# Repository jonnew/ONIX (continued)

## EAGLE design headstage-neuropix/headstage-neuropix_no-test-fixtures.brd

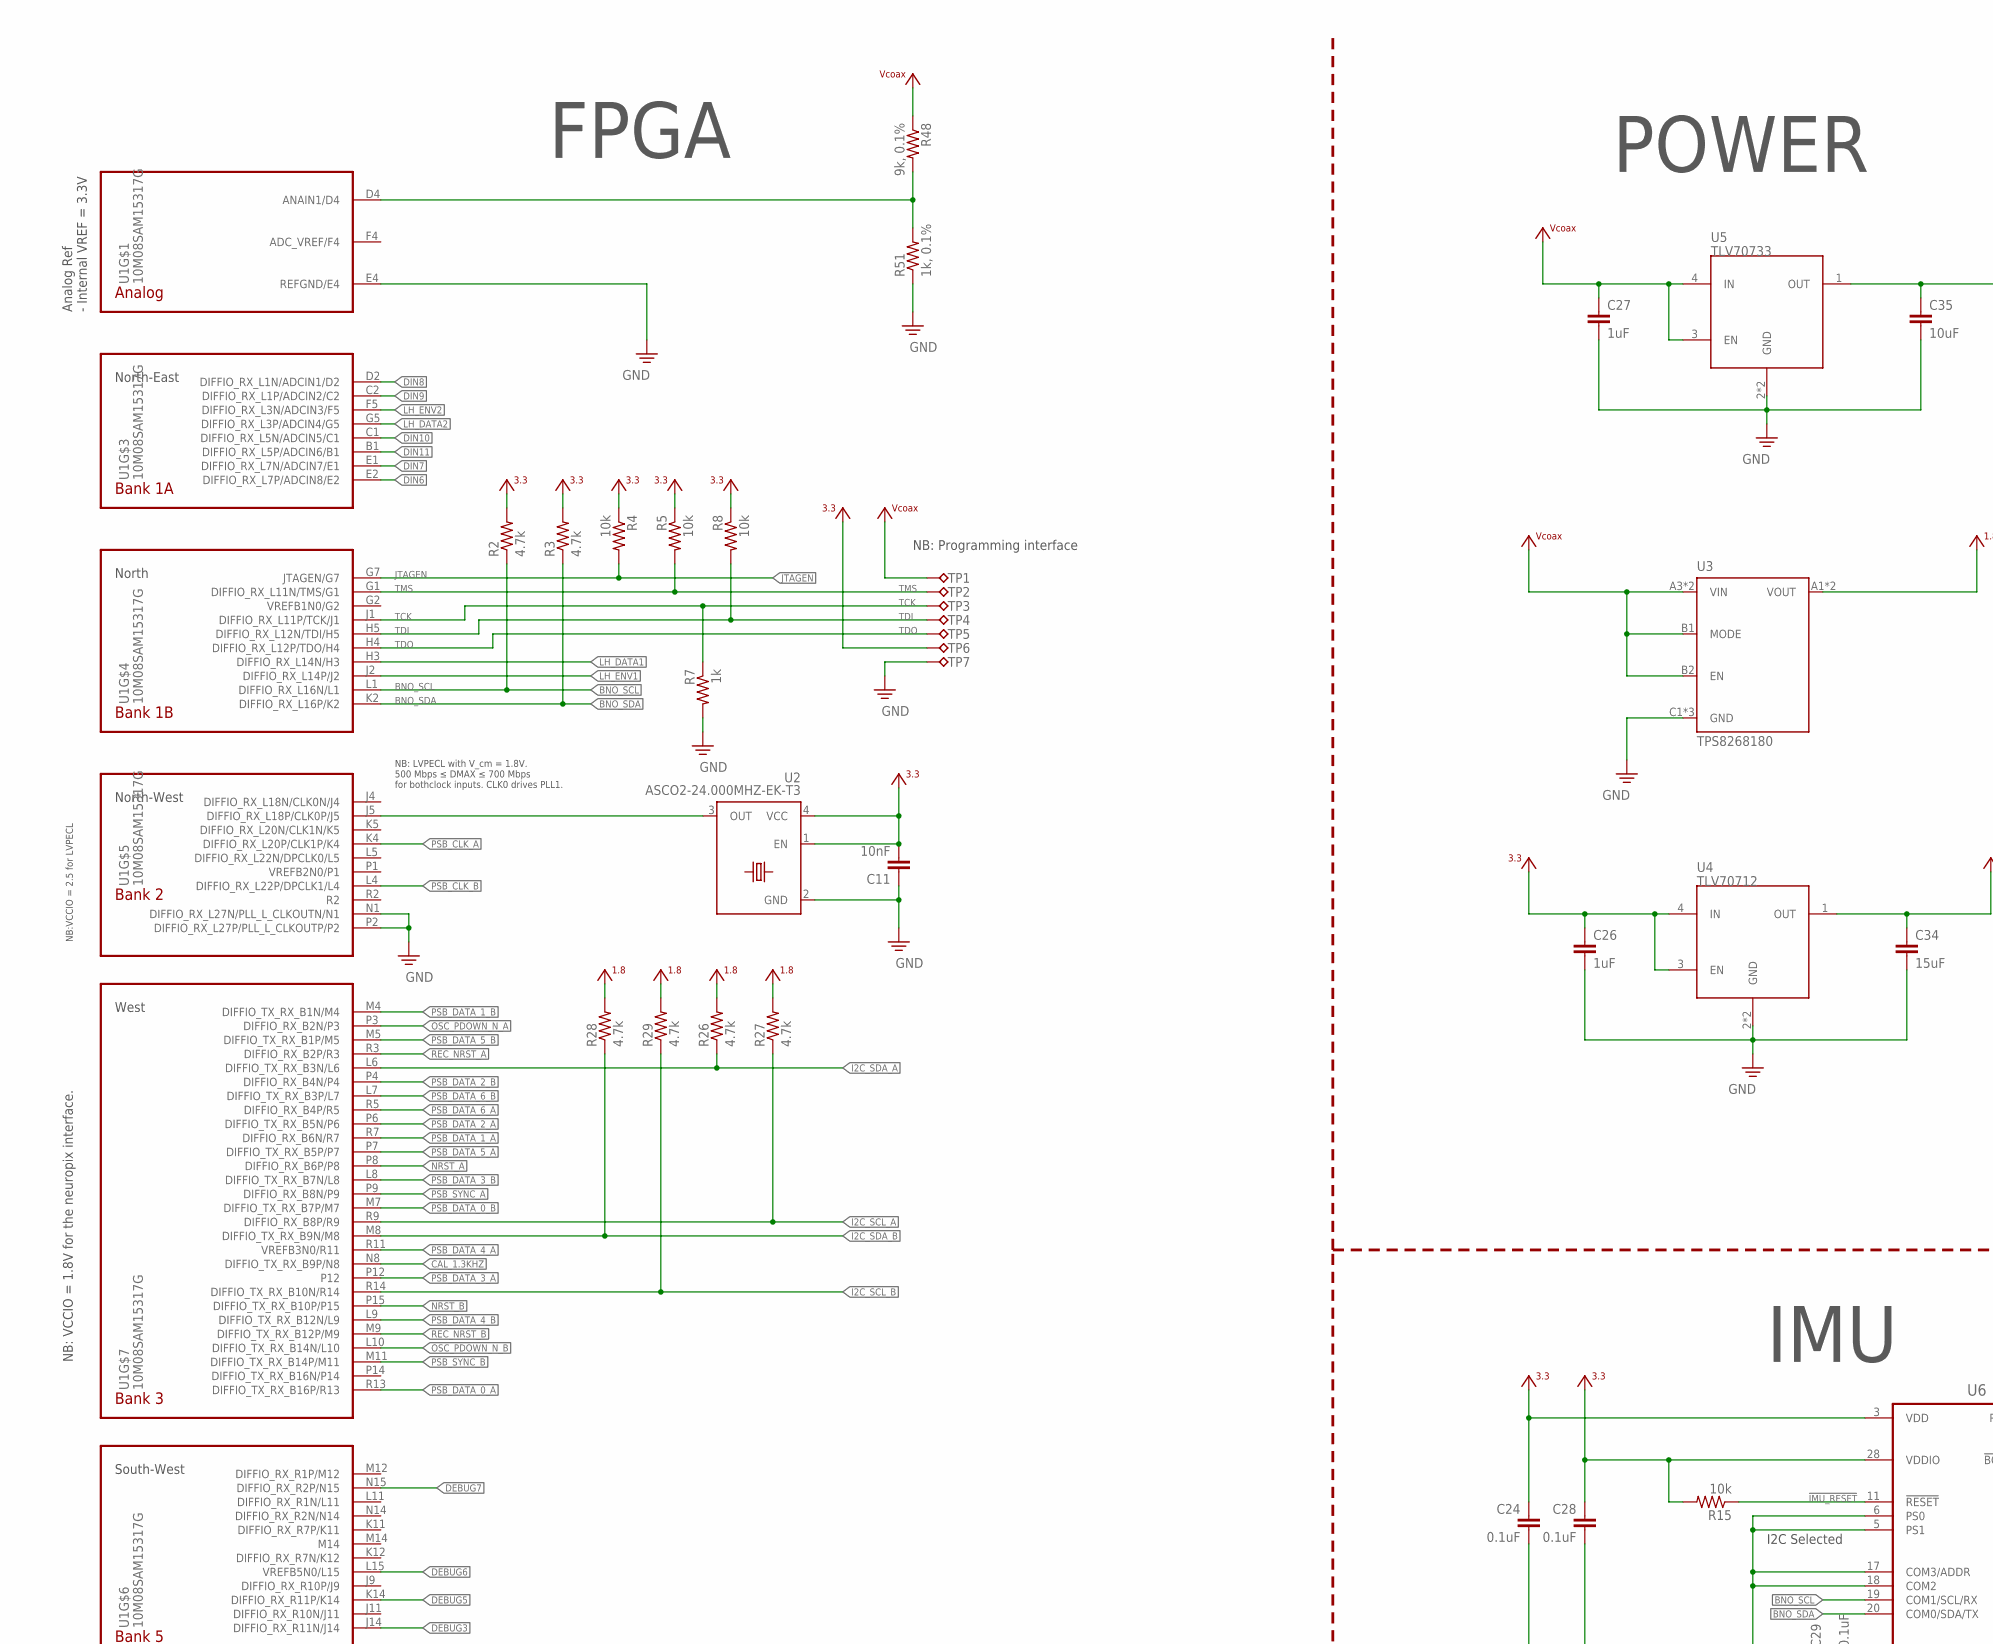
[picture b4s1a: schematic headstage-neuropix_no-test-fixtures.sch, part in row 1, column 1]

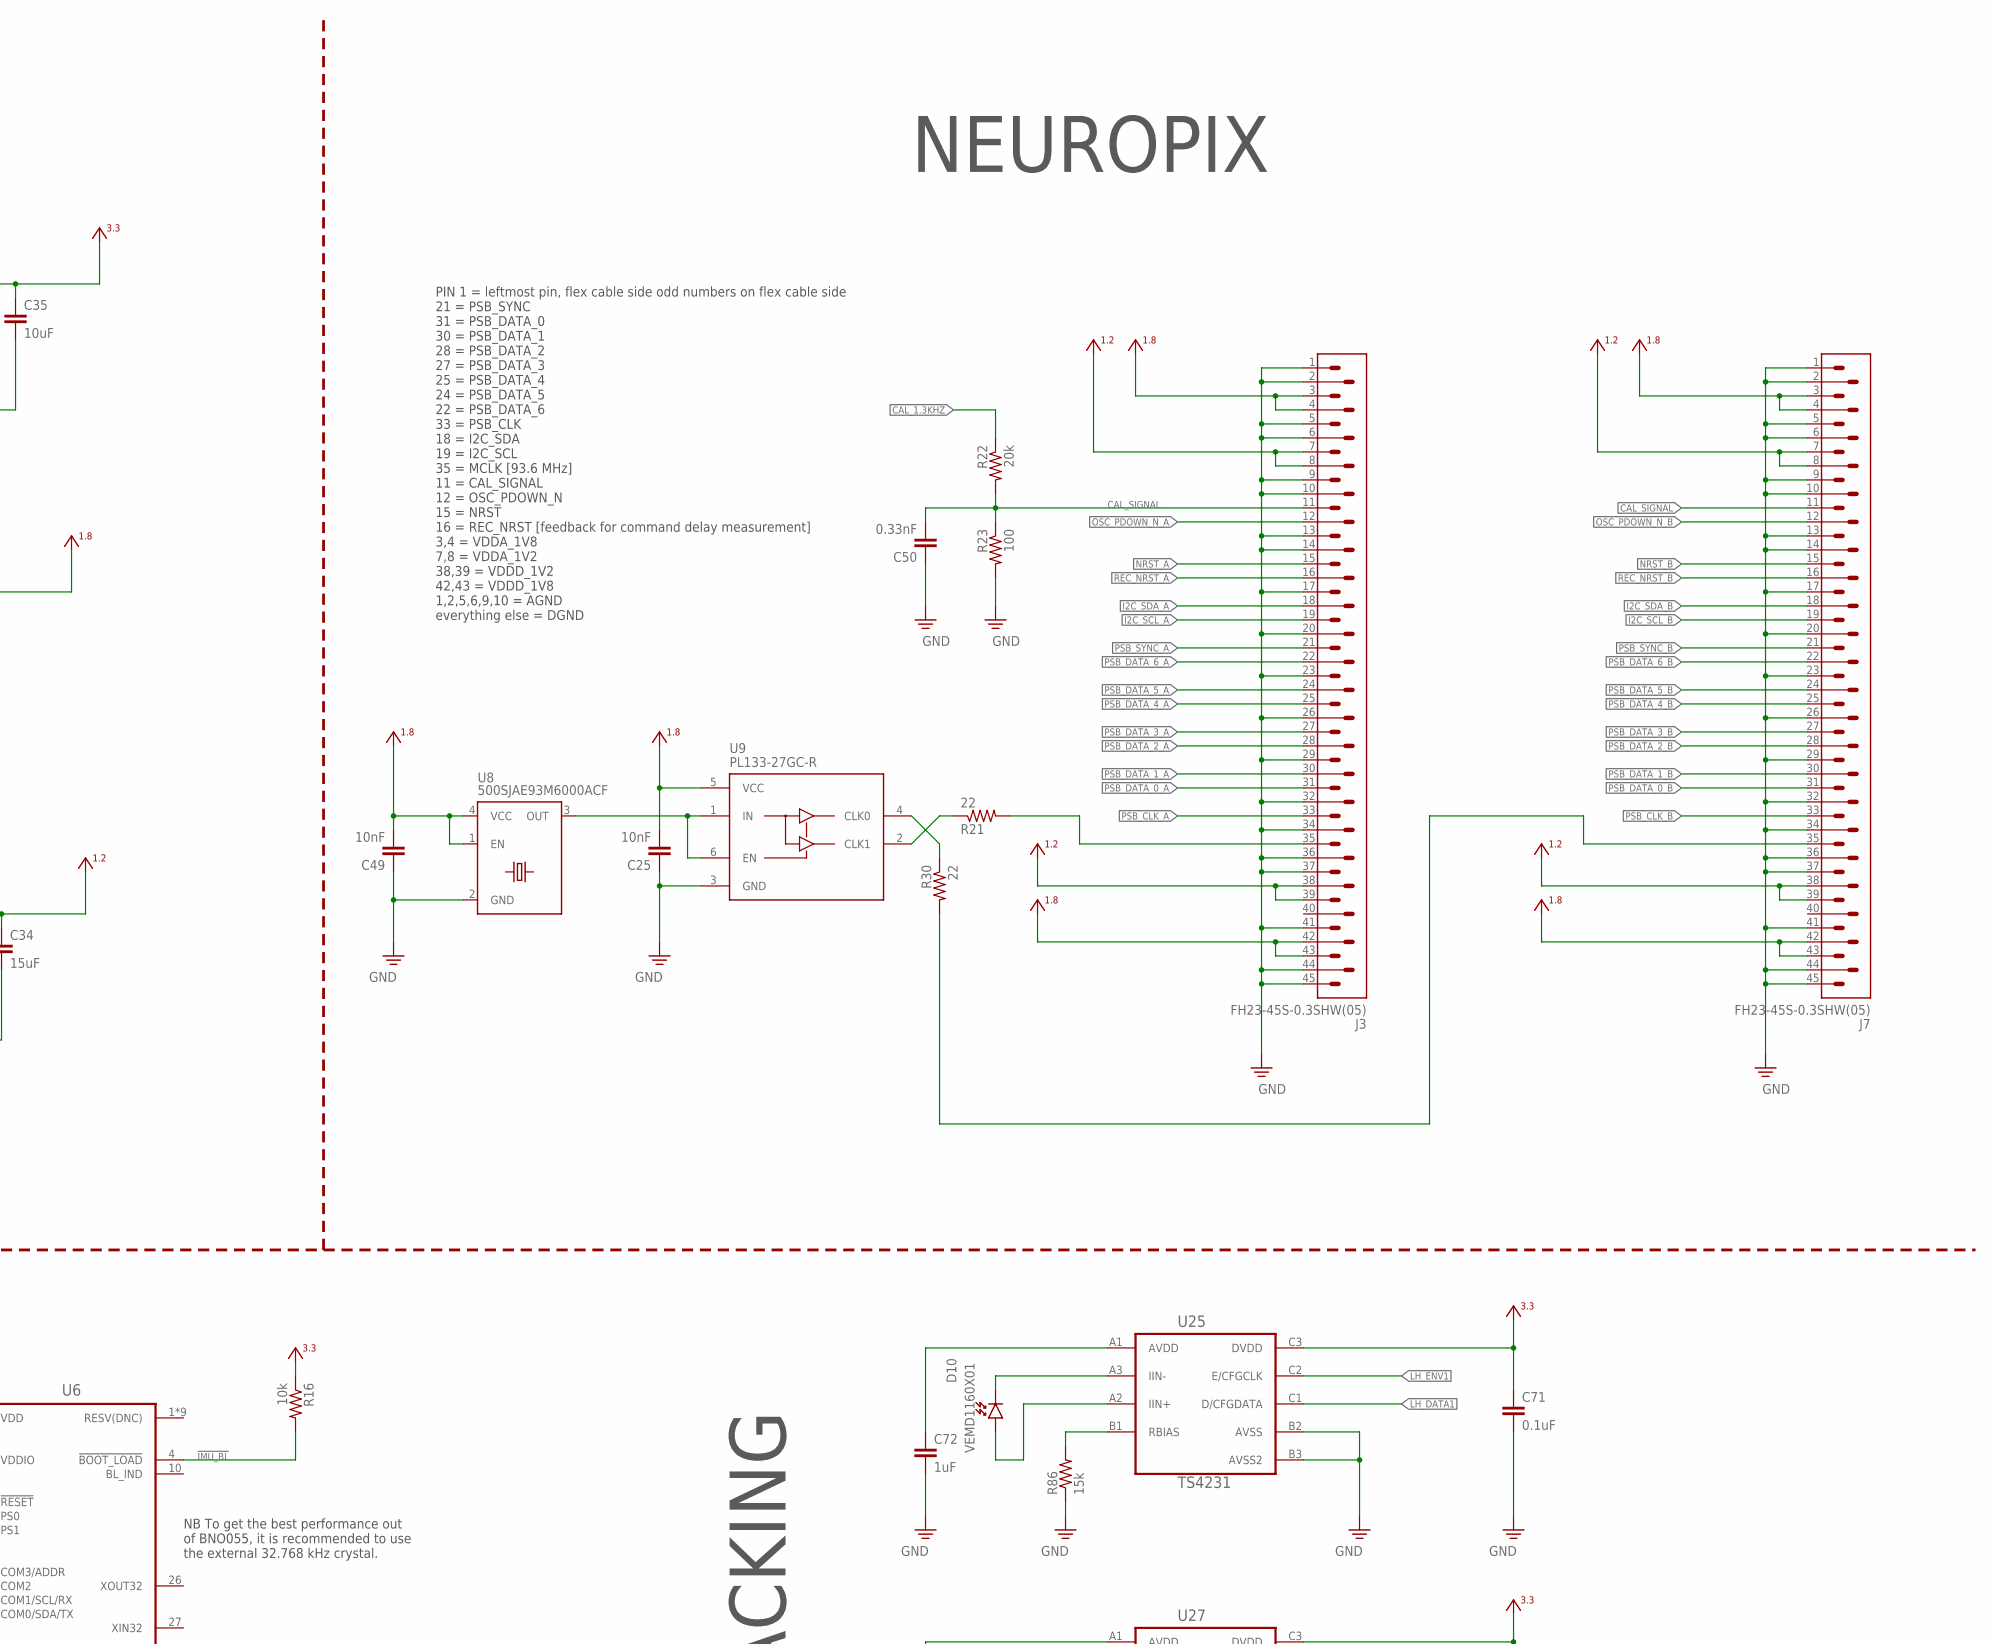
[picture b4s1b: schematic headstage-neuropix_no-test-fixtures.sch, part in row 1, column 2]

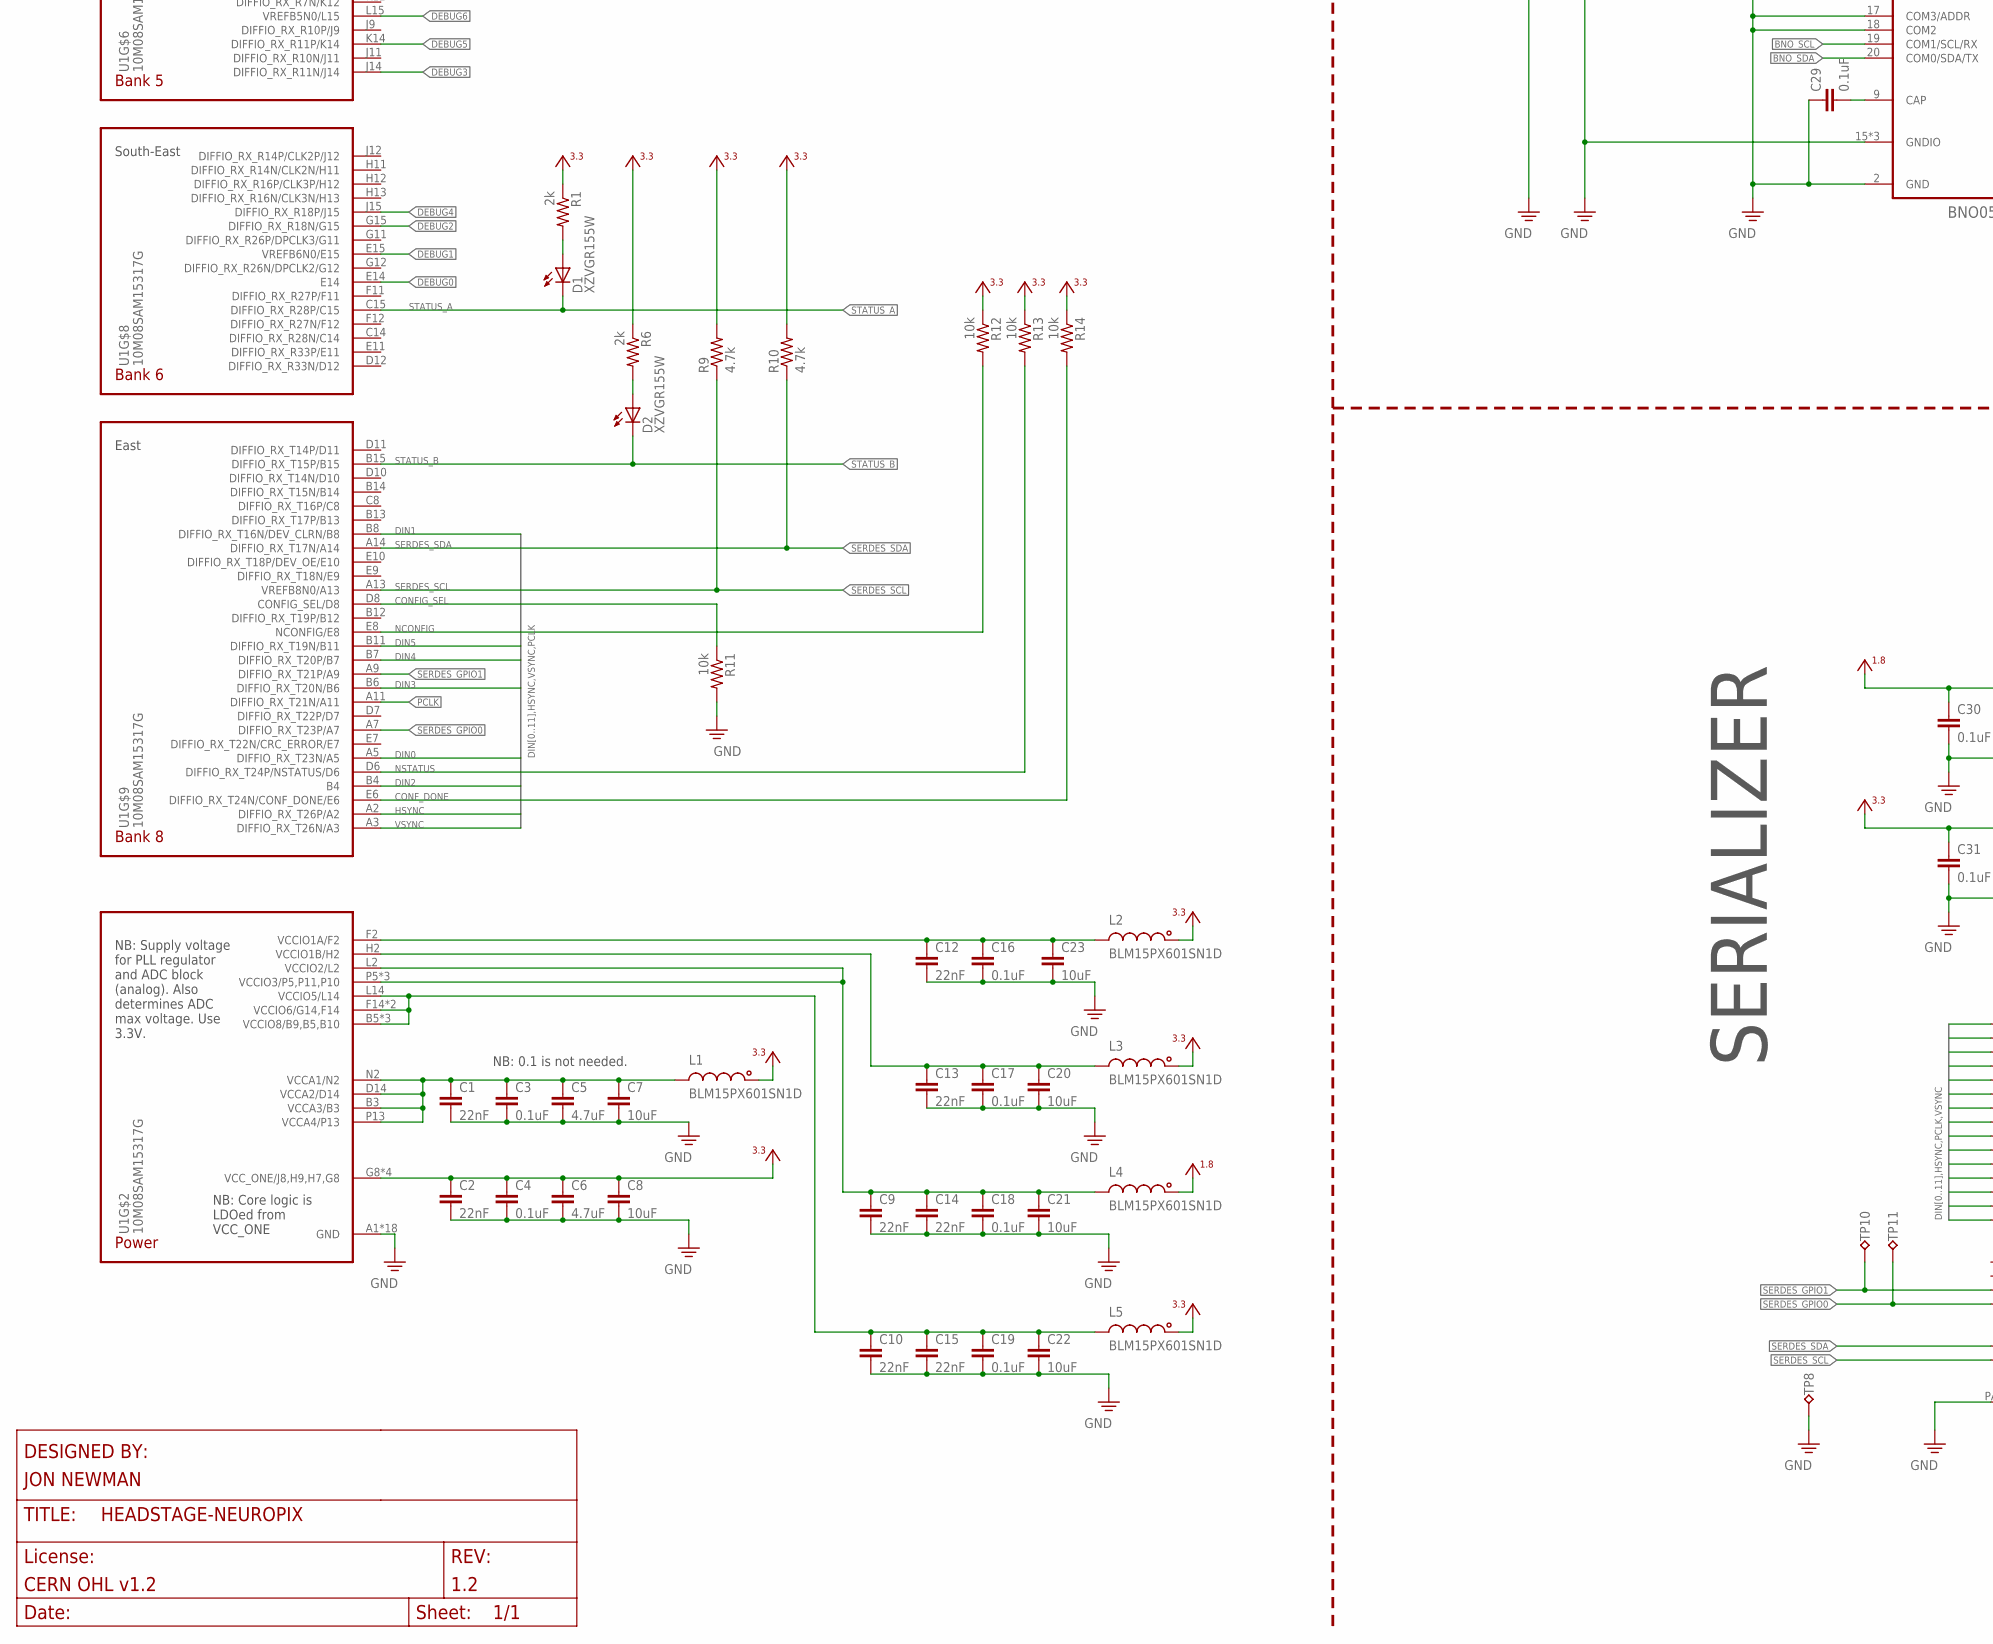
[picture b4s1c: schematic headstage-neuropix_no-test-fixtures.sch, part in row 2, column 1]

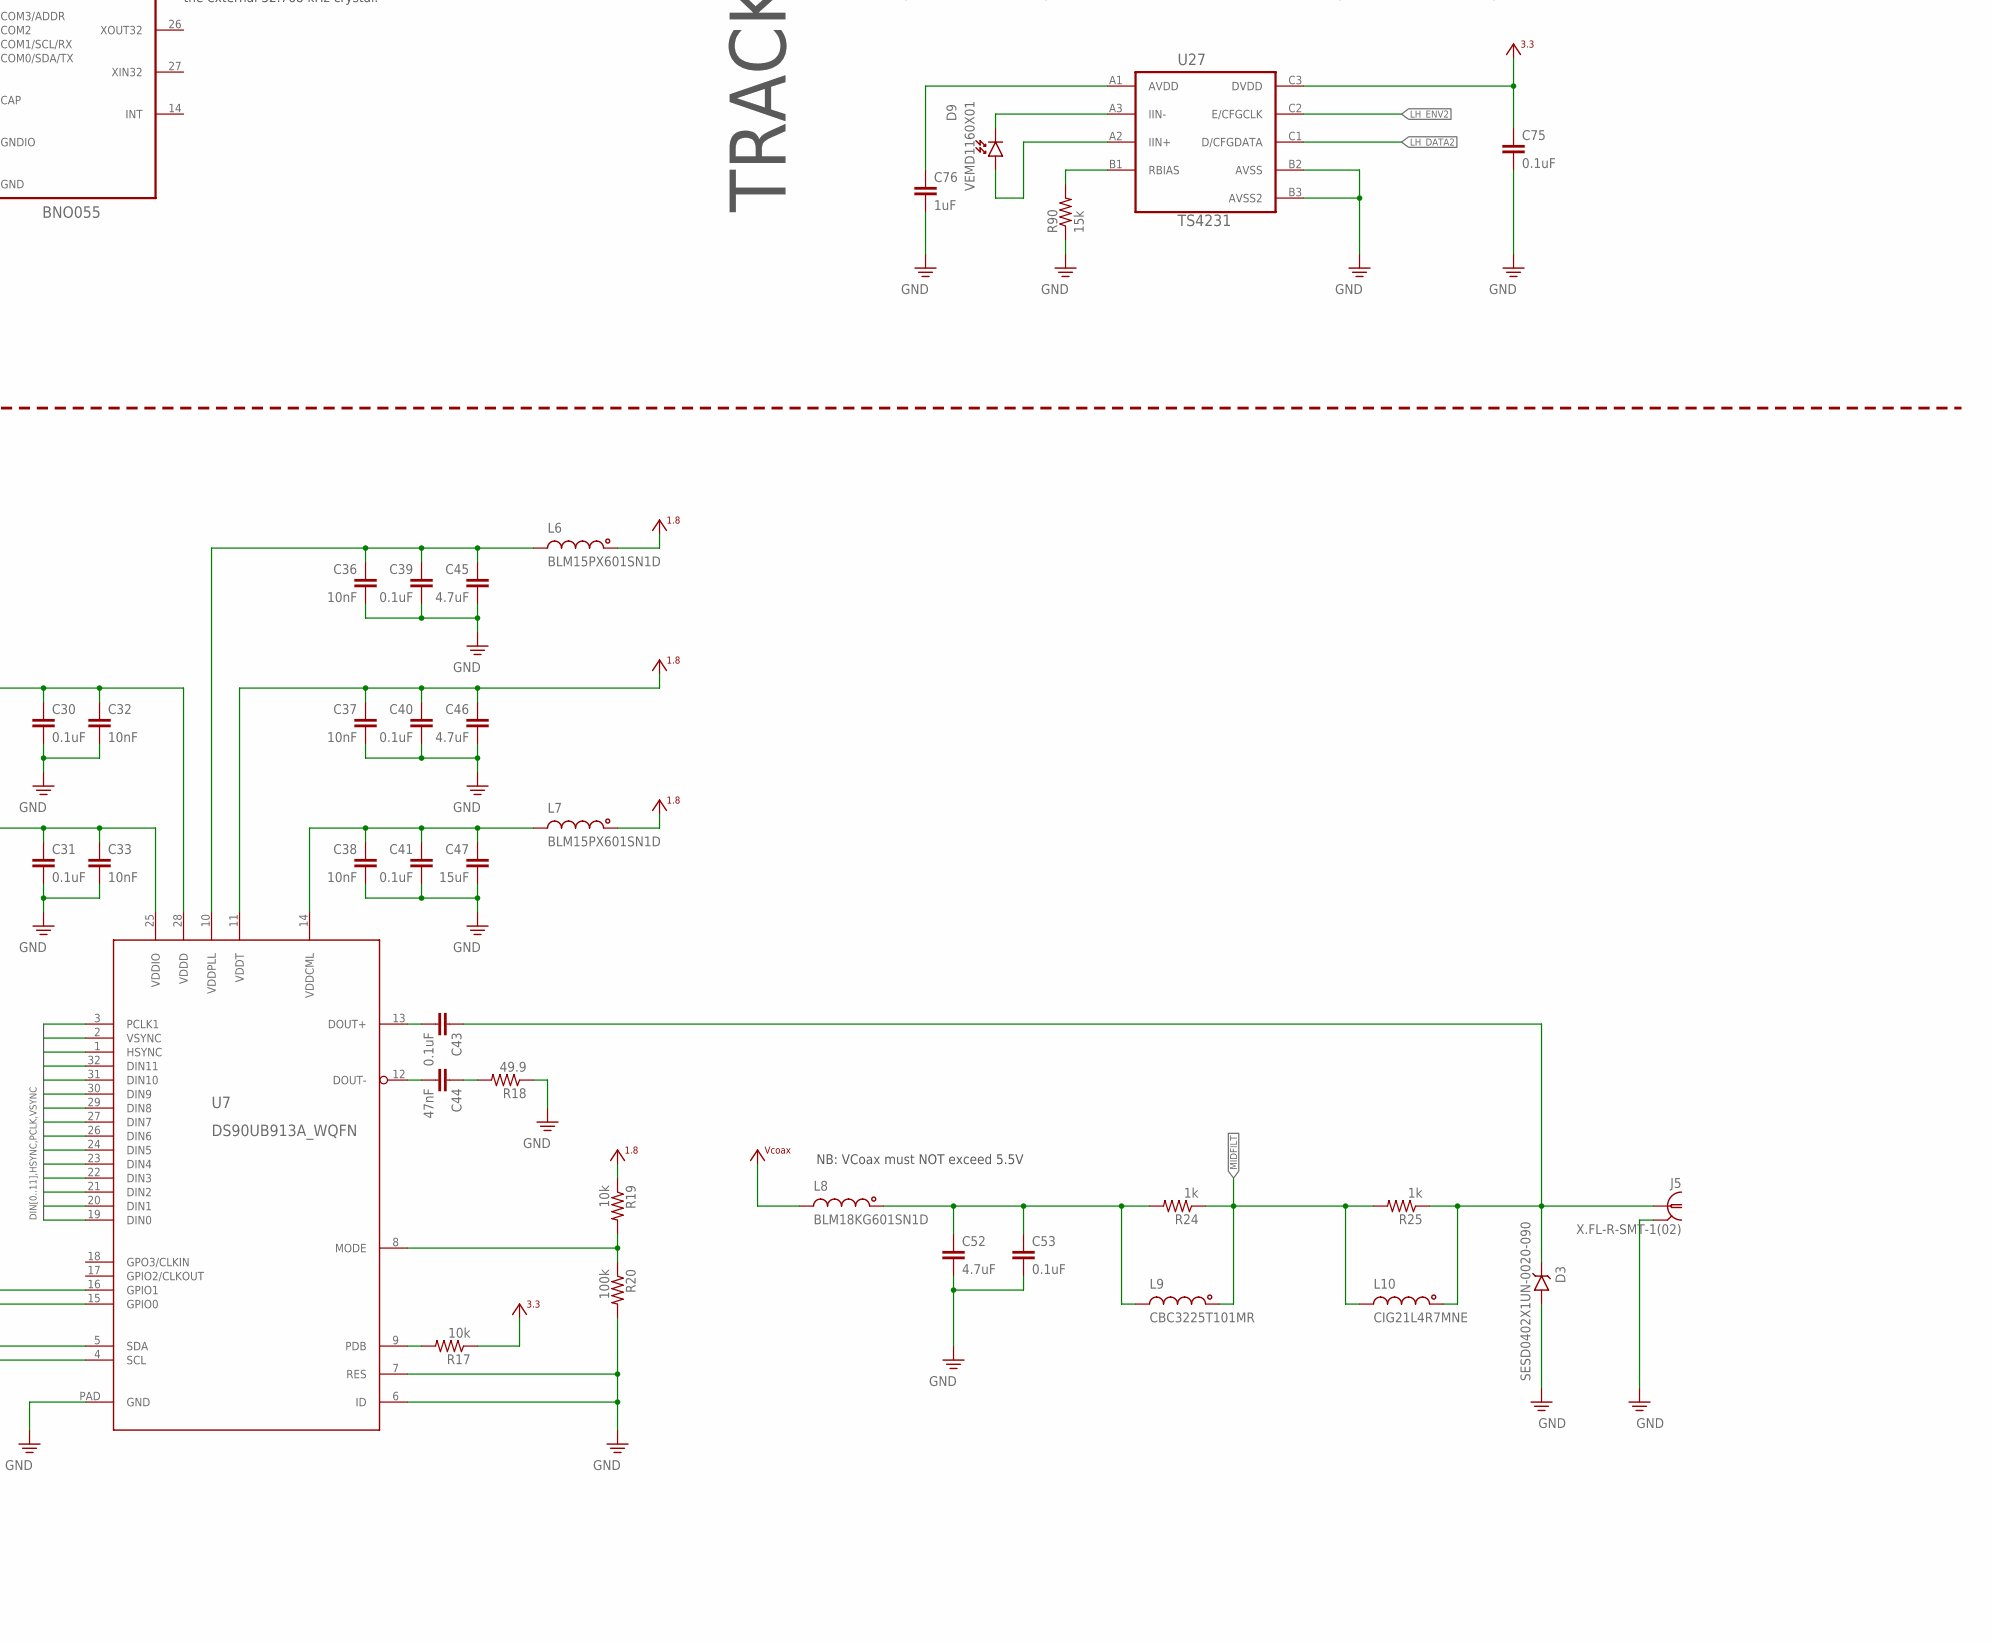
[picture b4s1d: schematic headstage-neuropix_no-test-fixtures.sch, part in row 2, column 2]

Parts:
C1, C2, C9, C10, C12, C13, C14, C15: 22nF; 0201T
C3, C4, C16, C17, C18, C19, C24, C28, C29, C30, C31, C39, C40, C41, C43, C53: 0.1uF; 0201T
C5, C6, C45, C46, C52: 4.7uF; 0402T
C7, C8, C20, C21, C22, C23, C35: 10uF; 0402T
C11, C25, C32, C33, C36, C37, C38, C49: 10nF; 0201T
C26, C27: 1uF; 0402T
C34, C47: 15uF; 0402TW
C44: 47nF; 0201T
C50: 0.33nF; 0201T
C71, C75: 0.1uF; 0201T; PARTNO C0603X5R1C104K030BC
C72, C76: 1uF; 0201T; PARTNO CL03A105MP3ZSNH
D1, D2: XZVGR155W; LED-0201T
D3: SESD0402X1UN-0020-090; 0402T-DFN
D9, D10: VEMD1160X01; 0805PT
J3, J7: FH23-45S-0.3SHW(05)
J5: X.FL-R-SMT-1(02); X_FL_R_SMT_1(02)
L1, L2, L3, L4, L5, L6, L7: BLM15PX601SN1D; 0402T
L8: BLM18KG601SN1D; 0603T
L9: CBC3225T101MR; 1210T
L10: CIG21L4R7MNE; 0805T
R1, R6: 2k; 0201T
R2, R3, R9, R10, R26, R27, R28, R29: 4.7k; 0201T
R4, R5, R8, R11, R12, R13, R14, R15, R16, R17, R19: 10k; 0201T
R7, R24, R25: 1k; 0201T
R18: 49.9; 0201T
R20: 100k; 0201T
R21, R30: 22; 0201T
R22: 20k; 0201T
R23: 100; 0201T
R48: 9k, 0.1%; 0201T
R51: 1k, 0.1%; 0201T
R86, R90: 15k; 0201T
TP1, TP2, TP3, TP4, TP5, TP6, TP7: TPTP10R; TP10R
TP8: TPTP11R; TP11R
TP10, TP11: TPTP09R; TP09R
U1: 10M08SAM15317G; MBGA153-8X8
U2: ASCO2-24.000MHZ-EK-T3; ASCO
U3: TPS8268180; MICROSIP9-3X2.3
U4: TLV70712; X2SON
U5: TLV70733; X2SON
U6: BNO055; LGA-28-3.8X5.2
U7: DS90UB913A_WQFN; WQFN32-5X5
U8: 500SJAE93M6000ACF; SIT8008BCA7-18E
U9: PL133-27GC-R; DFN6_2X1.3_PAD
U25, U27: TS4231; WLCSP3X3

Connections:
24MHZ_P: U1.J5 (DIFFIO_RX_L18P/CLK0P/J5), U2.3 (OUT)
!IMU_BL: R16.2, U6.4 (!BOOT_LOAD)
!IMU_RESET: R15.1, U6.11 (!RESET)
+1V2: C34.1, J3.7, J3.8, J3.38, J3.39, J7.7, J7.8, J7.38, J7.39, U4.1 (OUT)
+1V8: C25.2, C30.1, C32.1, C37.1, C40.1, C46.1, C49.2, J3.3, J3.4, J3.42, J3.43, J7.3, J7.4, J7.42, J7.43, L4.1, L6.1, L7.1, R19.1, R26.2, R27.2, R28.2, R29.2, U3.A1 (VOUT), U3.A2 (VOUT), U7.11 (VDDT), U7.28 (VDDD), U8.1 (EN), U8.4 (VCC), U9.5 (VCC)
+3V3: C2.1, C4.1, C6.1, C8.1, C11.2, C24.1, C26.1, C28.1, C31.1, C33.1, C35.1, C71.1, C75.1, L1.1, L2.1, L3.1, L5.1, R1.1, R2.2, R3.2, R4.1, R5.1, R6.1, R8.1, R9.2, R10.2, R12.1, R13.1, R14.1, R15.2, R16.1, R17.1, TP6.TP, U1.G8 (VCC_ONE/J8,H9,H7,G8), U1.H7 (VCC_ONE/J8,H9,H7,G8), U1.H9 (VCC_ONE/J8,H9,H7,G8), U1.J8 (VCC_ONE/J8,H9,H7,G8), U2.1 (EN), U2.4 (VCC), U4.3 (EN), U4.4 (IN), U5.1 (OUT), U6.3 (VDD), U6.28 (VDDIO), U7.25 (VDDIO), U25.C3 (DVDD), U27.C3 (DVDD)
BNO_SCL: R2.1, U1.L1 (DIFFIO_RX_L16N/L1), U6.19 (COM1/SCL/RX)
BNO_SDA: R3.1, U1.K2 (DIFFIO_RX_L16P/K2), U6.20 (COM0/SDA/TX)
CAL_1.3KHZ: R22.1, U1.N8 (DIFFIO_TX_RX_B9P/N8)
CAL_SIGNAL: C50.2, J3.11, J7.11, R22.2, R23.1
CONFIG_SEL: R11.1, U1.D8 (CONFIG_SEL/D8)
CONF_DONE: R14.2, U1.E6 (DIFFIO_RX_T24N/CONF_DONE/E6)
DEBUG0: U1.E14
DEBUG1: U1.E15 (VREFB6N0/E15)
DEBUG2: U1.G15 (DIFFIO_RX_R18N/G15)
DEBUG3: U1.J14 (DIFFIO_RX_R11N/J14)
DEBUG4: U1.J15 (DIFFIO_RX_R18P/J15)
DEBUG5: U1.K14 (DIFFIO_RX_R11P/K14)
DEBUG6: U1.L15 (VREFB5N0/L15)
DEBUG7: U1.N15 (DIFFIO_RX_R2P/N15)
DIN0: U1.A5 (DIFFIO_RX_T23N/A5), U7.19 (DIN0)
DIN1: U1.B8 (DIFFIO_RX_T16N/DEV_CLRN/B8), U7.20 (DIN1)
DIN2: U1.B4, U7.21 (DIN2)
DIN3: U1.B6 (DIFFIO_RX_T20N/B6), U7.22 (DIN3)
DIN4: U1.B7 (DIFFIO_RX_T20P/B7), U7.23 (DIN4)
DIN5: U1.B11 (DIFFIO_RX_T19N/B11), U7.24 (DIN5)
DIN6: U1.E2 (DIFFIO_RX_L7P/ADCIN8/E2), U7.26 (DIN6)
DIN7: U1.E1 (DIFFIO_RX_L7N/ADCIN7/E1), U7.27 (DIN7)
DIN8: U1.D2 (DIFFIO_RX_L1N/ADCIN1/D2), U7.29 (DIN8)
DIN9: U1.C2 (DIFFIO_RX_L1P/ADCIN2/C2), U7.30 (DIN9)
DIN10: U1.C1 (DIFFIO_RX_L5N/ADCIN5/C1), U7.31 (DIN10)
DIN11: U1.B1 (DIFFIO_RX_L5P/ADCIN6/B1), U7.32 (DIN11)
GND: C1.2, C2.2, C3.2, C4.2, C5.2, C6.2, C7.2, C8.2, C9.2, C10.2, C11.1, C12.2, C13.2, C14.2, C15.2, C16.2, C17.2, C18.2, C19.2, C20.2, C21.2, C22.2, C23.2, C24.2, C25.1, C26.2, C27.2, C28.2, C29.1, C30.2, C31.2, C32.2, C33.2, C34.2, C35.2, C36.2, C37.2, C38.2, C39.2, C40.2, C41.2, C45.2, C46.2, C47.2, C49.1, C50.1, C52.2, C53.2, C71.2, C72.2, C75.2, C76.2, D3.A, J3.1, J3.2, J3.5, J3.6, J3.9, J3.10, J3.13, J3.14, J3.17, J3.20, J3.23, J3.26, J3.29, J3.32, J3.34, J3.36, J3.37, J3.41, J3.44, J3.45, J5.P$2 (2), J5.P$3 (2), J5.P$4 (2), J7.1, J7.2, J7.5, J7.6, J7.9, J7.10, J7.13, J7.14, J7.17, J7.20, J7.23, J7.26, J7.29, J7.32, J7.34, J7.36, J7.37, J7.41, J7.44, J7.45, R7.2, R11.2, R18.1, R20.2, R23.2, R51.1, R86.1, R90.1, TP7.TP, TP8.TP, U1.A1 (GND), U1.A15 (GND), U1.B2 (GND), U1.D5 (GND), U1.D9 (GND), U1.E4 (REFGND/E4), U1.E5 (GND), U1.E12 (GND), U1.G4 (GND), U1.G9 (GND), U1.H8 (GND), U1.H14 (GND), U1.J7 (GND), U1.L12 (GND), U1.M2 (GND), U1.M6 (GND), U1.M10 (GND), U1.N1 (DIFFIO_RX_L27N/PLL_L_CLKOUTN/N1), U1.P2 (DIFFIO_RX_L27P/PLL_L_CLKOUTP/P2), U1.R1 (GND), U1.R15 (GND), U2.2 (GND), U3.C1 (GND), U3.C2 (GND), U3.C3 (GND), U4.2 (GND), U4.PAD (GND), U5.2 (GND), U5.PAD (GND), U6.2 (GND), U6.5 (PS1), U6.6 (PS0), U6.15 (GNDIO), U6.16 (GNDIO), U6.17 (COM3/ADDR), U6.18 (COM2), U6.25 (GNDIO), U7.6 (ID), U7.7 (RES), U7.PAD (GND), U8.2 (GND), U9.3 (GND), U25.B2 (AVSS), U25.B3 (AVSS2), U27.B2 (AVSS), U27.B3 (AVSS2)
HSYNC: U1.A2 (DIFFIO_RX_T26P/A2), U7.1 (HSYNC)
I2C_SCL_A: J3.19, R27.1, U1.R9 (DIFFIO_RX_B8P/R9)
I2C_SCL_B: J7.19, R29.1, U1.R14 (DIFFIO_TX_RX_B10N/R14)
I2C_SDA_A: J3.18, R26.1, U1.L6 (DIFFIO_TX_RX_B3N/L6)
I2C_SDA_B: J7.18, R28.1, U1.M8 (DIFFIO_TX_RX_B9N/M8)
JTAGEN: R4.2, U1.G7 (JTAGEN/G7)
LH_DATA1: U1.H3 (DIFFIO_RX_L14N/H3), U25.C1 (D/CFGDATA)
LH_DATA2: U1.G5 (DIFFIO_RX_L3P/ADCIN4/G5), U27.C1 (D/CFGDATA)
LH_ENV1: U1.J2 (DIFFIO_RX_L14P/J2), U25.C2 (E/CFGCLK)
LH_ENV2: U1.F5 (DIFFIO_RX_L3N/ADCIN3/F5), U27.C2 (E/CFGCLK)
MIDFILT: L9.1, L10.2, R24.1, R25.2
unnamed: U8.3 (OUT), U9.1 (IN), U9.6 (EN)
unnamed: R30.1, U9.4 (CLK0)
unnamed: J3.35, R21.2
unnamed: C13.1, C17.1, C20.1, L3.2, U1.H2 (VCCIO1B/H2)
unnamed: J7.35, R30.2
unnamed: R21.1, U9.2 (CLK1)
unnamed: D10.C, U25.A3 (IIN-)
unnamed: D10.A, U25.A2 (IIN+)
unnamed: R86.2, U25.B1 (RBIAS)
unnamed: C72.1, U25.A1 (AVDD)
unnamed: C52.1, C53.1, L8.1, L9.2, R24.2
unnamed: D9.C, U27.A3 (IIN-)
unnamed: D9.A, U27.A2 (IIN+)
unnamed: R90.2, U27.B1 (RBIAS)
unnamed: C43.2, U7.13 (DOUT+)
unnamed: R17.2, U7.9 (PDB)
unnamed: C44.2, U7.12 (DOUT-)
unnamed: C44.1, R18.2
unnamed: R19.2, R20.1, U7.8 (MODE)
unnamed: C36.1, C39.1, C45.1, L6.2, U7.10 (VDDPLL)
unnamed: C38.1, C41.1, C47.1, L7.2, U7.14 (VDDCML)
unnamed: C76.1, U27.A1 (AVDD)
unnamed: R48.2, R51.2, U1.D4 (ANAIN1/D4)
unnamed: C29.2, U6.9 (CAP)
unnamed: D2.2 (A), R6.2
unnamed: D1.2 (A), R1.2
NCONFIG: R12.2, U1.E8 (NCONFIG/E8)
NRST_A: J3.15, U1.P8 (DIFFIO_RX_B6P/P8)
NRST_B: J7.15, U1.P15 (DIFFIO_TX_RX_B10P/P15)
NSTATUS: R13.2, U1.D6 (DIFFIO_RX_T24P/NSTATUS/D6)
OSC_PDOWN_N_A: J3.12, U1.P3 (DIFFIO_RX_B2N/P3)
OSC_PDOWN_N_B: J7.12, U1.L10 (DIFFIO_TX_RX_B14N/L10)
PCLK: U1.A11 (DIFFIO_RX_T21N/A11), U7.3 (PCLK1)
PSB_CLK_A: J3.33, U1.K4 (DIFFIO_RX_L20P/CLK1P/K4)
PSB_CLK_B: J7.33, U1.L4 (DIFFIO_RX_L22P/DPCLK1/L4)
PSB_DATA_0_A: J3.31, U1.R13 (DIFFIO_TX_RX_B16P/R13)
PSB_DATA_0_B: J7.31, U1.M7 (DIFFIO_TX_RX_B7P/M7)
PSB_DATA_1_A: J3.30, U1.R7 (DIFFIO_RX_B6N/R7)
PSB_DATA_1_B: J7.30, U1.M4 (DIFFIO_TX_RX_B1N/M4)
PSB_DATA_2_A: J3.28, U1.P6 (DIFFIO_TX_RX_B5N/P6)
PSB_DATA_2_B: J7.28, U1.P4 (DIFFIO_RX_B4N/P4)
PSB_DATA_3_A: J3.27, U1.P12
PSB_DATA_3_B: J7.27, U1.L8 (DIFFIO_TX_RX_B7N/L8)
PSB_DATA_4_A: J3.25, U1.R11 (VREFB3N0/R11)
PSB_DATA_4_B: J7.25, U1.L9 (DIFFIO_TX_RX_B12N/L9)
PSB_DATA_5_A: J3.24, U1.P7 (DIFFIO_TX_RX_B5P/P7)
PSB_DATA_5_B: J7.24, U1.M5 (DIFFIO_TX_RX_B1P/M5)
PSB_DATA_6_A: J3.22, U1.R5 (DIFFIO_RX_B4P/R5)
PSB_DATA_6_B: J7.22, U1.L7 (DIFFIO_TX_RX_B3P/L7)
PSB_SYNC_A: J3.21, U1.P9 (DIFFIO_RX_B8N/P9)
PSB_SYNC_B: J7.21, U1.M11 (DIFFIO_TX_RX_B14P/M11)
REC_NRST_A: J3.16, U1.R3 (DIFFIO_RX_B2P/R3)
REC_NRST_B: J7.16, U1.M9 (DIFFIO_TX_RX_B12P/M9)
SERDES_GPIO0: TP11.TP, U1.A7 (DIFFIO_RX_T23P/A7), U7.15 (GPIO0)
SERDES_GPIO1: TP10.TP, U1.A9 (DIFFIO_RX_T21P/A9), U7.16 (GPIO1)
SERDES_SCL: R9.1, U1.A13 (VREFB8N0/A13), U7.4 (SCL)
SERDES_SDA: R10.1, U1.A14 (DIFFIO_RX_T17N/A14), U7.5 (SDA)
SIGOUT: C43.1, D3.C, J5.P$1 (1), L10.1, R25.1
STATUS_A: D1.1 (C), U1.C15 (DIFFIO_RX_R28P/C15)
STATUS_B: D2.1 (C), U1.B15 (DIFFIO_RX_T15P/B15)
TCK: R7.1, TP3.TP, U1.J1 (DIFFIO_RX_L11P/TCK/J1)
TDI: R8.2, TP4.TP, U1.H5 (DIFFIO_RX_L12N/TDI/H5)
TDO: TP5.TP, U1.H4 (DIFFIO_RX_L12P/TDO/H4)
TMS: R5.2, TP2.TP, U1.G1 (DIFFIO_RX_L11N/TMS/G1)
VCCA: C1.1, C3.1, C5.1, C7.1, L1.2, U1.B3 (VCCA3/B3), U1.D14 (VCCA2/D14), U1.N2 (VCCA1/N2), U1.P13 (VCCA4/P13)
VCCIO: C10.1, C15.1, C19.1, C22.1, L5.2, U1.B5 (VCCIO8/B9,B5,B10), U1.B9 (VCCIO8/B9,B5,B10), U1.B10 (VCCIO8/B9,B5,B10), U1.F14 (VCCIO6/G14,F14), U1.G14 (VCCIO6/G14,F14), U1.L14 (VCCIO5/L14)
VCCIO2: C9.1, C14.1, C18.1, C21.1, L4.2, U1.L2 (VCCIO2/L2), U1.P5 (VCCIO3/P5,P11,P10), U1.P10 (VCCIO3/P5,P11,P10), U1.P11 (VCCIO3/P5,P11,P10)
VCCIOA: C12.1, C16.1, C23.1, L2.2, U1.F2 (VCCIO1A/F2)
VCOAX: C27.1, L8.2, R48.1, TP1.TP, U3.A3 (VIN), U3.B1 (MODE), U3.B2 (EN), U3.B3 (VIN), U5.3 (EN), U5.4 (IN)
VSYNC: U1.A3 (DIFFIO_RX_T26N/A3), U7.2 (VSYNC)

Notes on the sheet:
NB: VCoax must NOT exceed 5.5V
SERIALIZER
POWER
NEUROPIX
PIN 1 = leftmost pin, flex cable side odd numbers on flex cable side 21 = PSB_SYNC 31 = PSB_DATA_0 30 = PSB_DATA_1 28 = PSB_DATA_2 27 = PSB_DATA_3 25 = PSB_DATA_4 24 = PSB_DATA_5 22 = PSB_DATA_6 33 = PSB_CLK 18 = I2C_SDA 19 = I2C_SCL 35 = MCLK [93.6 MHz] 11 = CAL_SIGNAL 12 = OSC_PDOWN_N 15 = NRST 1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
NB: Core logic is LDOed from VCC_ONE
NB: Supply voltage for PLL regulator and ADC block (analog). Also determines ADC max voltage. Use 3.3V.
NB: VCCIO = 1.8V for the neuropix interface.
FPGA
South-East
East
South-West
West
North-West
North
North-East
Analog Ref - Internal VREF = 3.3V
NB: Programming interface
NB: 0.1 is not needed.
NB:VCCIO = 2.5 for LVPECL
NB: LVPECL with V_cm = 1.8V. 500 Mbps ≤ DMAX ≤ 700 Mbps for bothclock inputs. CLK0 drives PLL1.
IMU
I2C Selected
NB To get the best performance out of BNO055, it is recommended to use the external 32.768 kHz crystal.
TRACKING

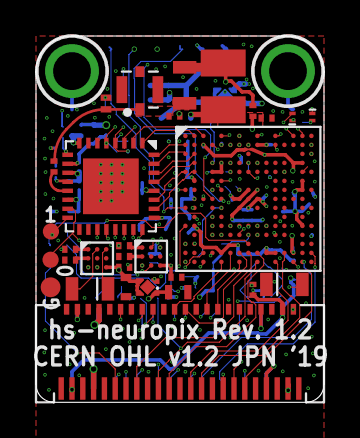
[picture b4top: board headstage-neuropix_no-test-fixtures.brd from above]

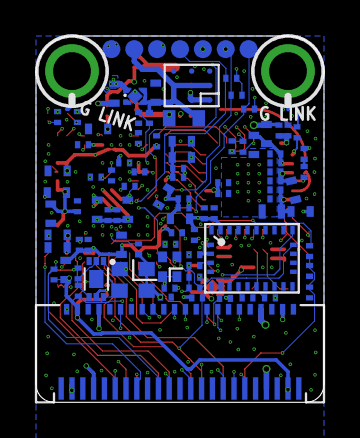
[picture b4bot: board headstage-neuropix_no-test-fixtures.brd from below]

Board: 6 copper layers, 16.0 x 20.4 mm, 127 parts (97 on the bottom side), 106 nets.
